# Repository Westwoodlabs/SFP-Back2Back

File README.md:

# SFP Back2Back V2

Bridges two small Form-factor Pluggable (SFP, Mini-GBIC) Modules together. This PCB makes it possible, for example, to switch from multi-mode to single-mode if one side has a built-in multi-mode transceiver, the range can be increased with a single-mode connection.  

## PCB

## Case

## Credits

This is a revised version of [git.binary-kitchen.de/tom/sfp_back2back](https://git.binary-kitchen.de/tom/sfp_back2back), because due to the global chip shortage in 2022 a change of the components was necessary. In this same process, small improvements were also made (Routing, I2C Headers, upgrade to 0805).

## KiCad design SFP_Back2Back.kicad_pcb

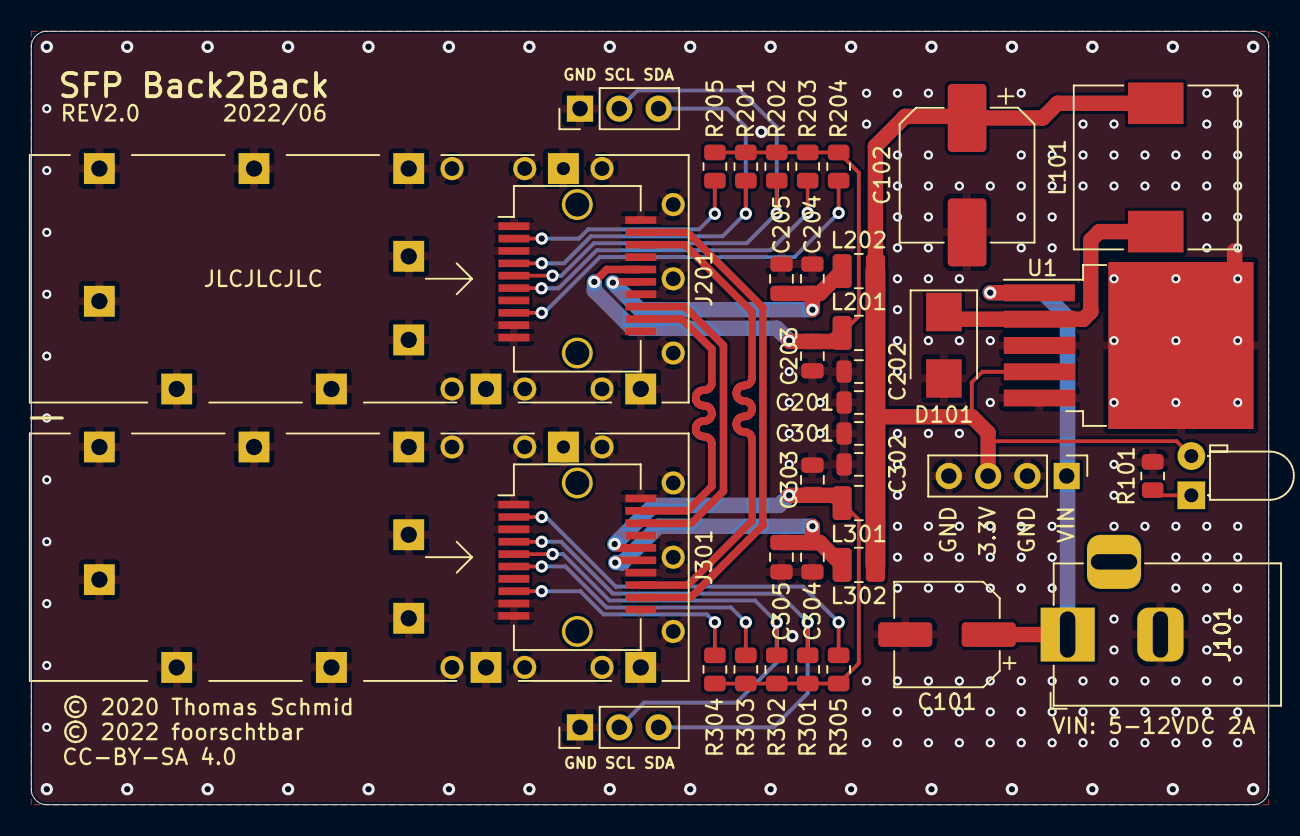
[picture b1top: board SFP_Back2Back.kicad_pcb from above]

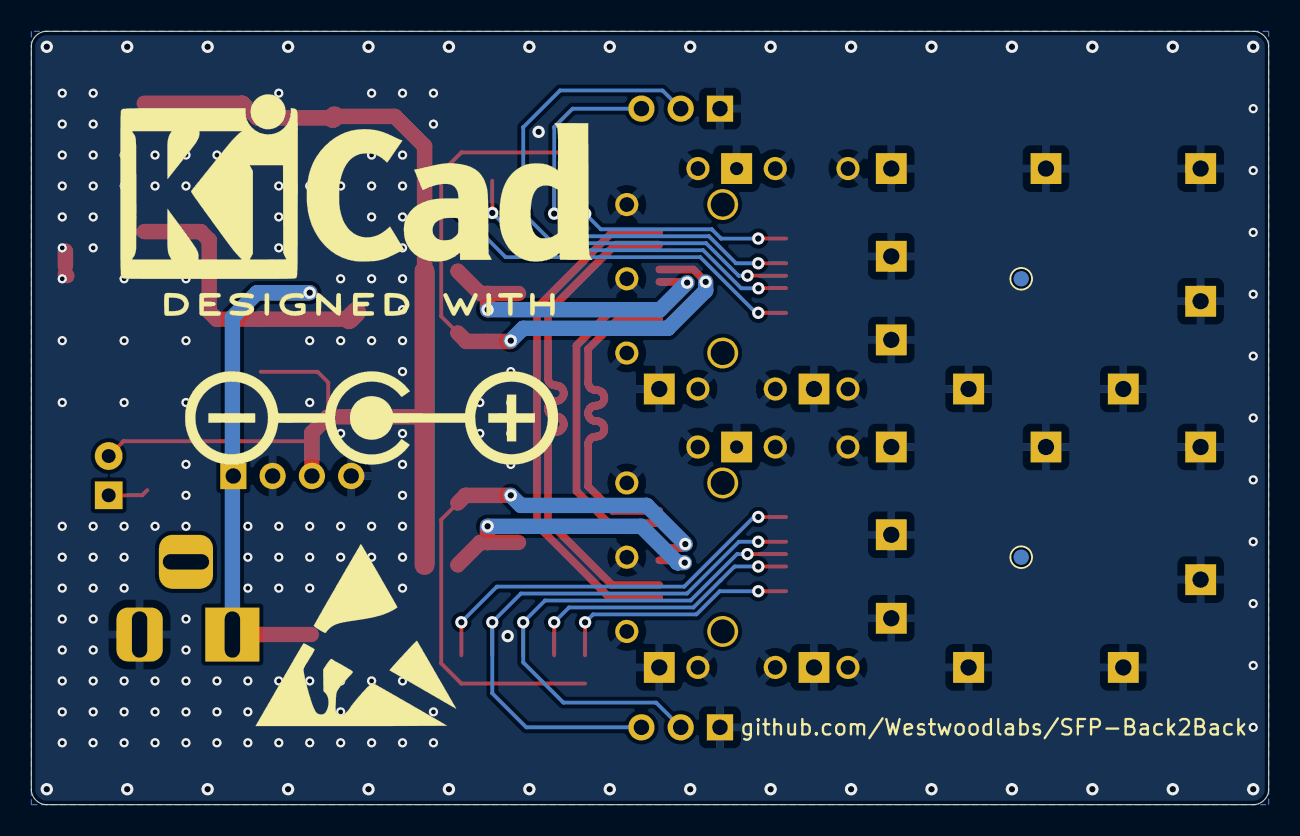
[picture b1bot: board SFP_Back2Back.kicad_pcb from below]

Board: 2 copper layers, 80.0 x 50.0 mm, 39 parts (2 on the bottom side), 23 nets.

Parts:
C101: 100uF; CP_Elec_6.3x7.7
C102: 1000uF; CP_Elec_8x10.5
C201, C204, C301, C304: 10uF; C_0805_2012Metric
C202, C203, C205, C302, C303, C305: 100nF; C_0805_2012Metric
D101: B340B-13-F; D_SMB
D103: LED; LED_D3.0mm_Horizontal_O1.27mm_Z2.0mm
J1: Conn_01x04; PinHeader_1x04_P2.54mm_Vertical
J2, J3: Conn_01x03; PinHeader_1x03_P2.54mm_Vertical
J101: Barrel_Jack; BarrelJack_Horizontal
J201, J301: SFP; Connector_SFP_and_Cage
L101: 100uH; L_10.4x10.4_H4.8
L201, L202, L301, L302: 1uH; L_1008_2520Metric
N1, N2: Housing_Pad; TestPoint_Pad_D1.0mm
R101: 68R; R_0805_2012Metric
R201, R202, R203, R204, R205, R301, R302, R303, R304, R305: 4.7k; R_0805_2012Metric
U1: LM2576S-3.3; TO-263-5_TabPin3

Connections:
+3V3: C102.1, C201.1, C202.1, C301.1, C302.1, D103.2 (A), J1.3, L101.2, L201.1, L202.1, L301.1, L302.1, U1.4 (FB)
/Vin: C101.1, J1.1, J101.1, U1.1 (VIN)
/sfp_module_1/MOD_DEF1_SCL: J2.2, J301.5 (MOD_DEF1), R302.1
/sfp_module_1/MOD_DEF2_SDA: J2.3, J301.4 (MOD_DEF2), R301.1
/sfp_module_1/RX+: J201.18 (TD+), J301.13 (RD+)
/sfp_module_1/RX-: J201.19 (TD-), J301.12 (RD-)
/sfp_module_1/RX_LOS: J301.8 (RX_LOS), R304.1
/sfp_module_1/TX+: J201.13 (RD+), J301.18 (TD+)
/sfp_module_1/TX-: J201.12 (RD-), J301.19 (TD-)
/sfp_module_1/TX_FAULT: J301.2 (TX_FAULT), R305.2
/sfp_module_1/VCC_R: C304.1, C305.1, J301.15 (VccR), L302.2
/sfp_module_1/VCC_T: C303.1, J301.16 (VccT), L301.2, R301.2, R302.2, R303.2, R304.2, R305.1
/sfp_module_2/MOD_DEF1_SCL: J3.2, J201.5 (MOD_DEF1), R202.1
/sfp_module_2/MOD_DEF2_SDA: J3.3, J201.4 (MOD_DEF2), R201.1
/sfp_module_2/RX_LOS: J201.8 (RX_LOS), R204.1
/sfp_module_2/TX_FAULT: J201.2 (TX_FAULT), R205.2
/sfp_module_2/VCC_R: C204.1, C205.1, J201.15 (VccR), L202.2
/sfp_module_2/VCC_T: C203.1, J201.16 (VccT), L201.2, R201.2, R202.2, R203.2, R204.2, R205.1
GND: C101.2, C102.2, C201.2, C202.2, C203.2, C204.2, C205.2, C301.2, C302.2, C303.2, C304.2, C305.2, D101.2 (A), J1.2, J1.4, J2.1, J3.1, J101.2, J201.1 (VeeT), J201.3 (TX_DISABLE), J201.9 (VeeR), J201.10 (VeeR), J201.11 (VeeR), J201.14 (VeeR), J201.17 (VeeT), J201.20 (VeeT), J201.CAGE, J301.1 (VeeT), J301.3 (TX_DISABLE), J301.9 (VeeR), J301.10 (VeeR), J301.11 (VeeR), J301.14 (VeeR), J301.17 (VeeT), J301.20 (VeeT), J301.CAGE, R101.2, U1.3 (GND), U1.5 (~ON/OFF)
unnamed: D101.1 (K), L101.1, U1.2 (OUT)
unnamed: D103.1 (K), R101.1
unnamed: J201.6 (MOD_DEF0), R203.1
unnamed: J301.6 (MOD_DEF0), R303.1

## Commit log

2020-11-29 finish layout
2021-01-10 fix unconnected tx disable pin
2021-01-10 add ibom
2021-01-10 add gitignore and remove unnecessary files
2021-01-26 add cad files for case
2022-05-19 Added README
2022-05-19 Fixed Typo in README
2022-05-19 Converter to KiCad 6 and added Symbol for alternative Buck-Converter
2022-05-19 Replaced Mouser with LCSC Components
2022-05-28 Added specifications
2022-05-28 Added I2C pins
2022-06-11 Added DC Jack 3D Model
2022-06-11 Added Case
2022-06-11 Moved Case STLs
2022-06-11 Updated gitignore
2022-06-11 Added DC-DC-Converter Datasheet
2022-06-11 Removed old BOM
2022-06-11 Finished PCB and renamed it
2022-06-11 Added Gerber files
2022-06-11 Fixed Caps Voltage
2022-06-11 Updated iBOM
2022-06-24 Fixed LCSC Order Number for 68R Resistor
2022-06-25 Added new housing/case
2022-06-26 Minor changes at the case

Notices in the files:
SFP_Back2Back.kicad_pcb:
© foorschtbar
© 2020 Thomas Schmid
© 2022 foorschtbar
CC-BY-SA 4.0
